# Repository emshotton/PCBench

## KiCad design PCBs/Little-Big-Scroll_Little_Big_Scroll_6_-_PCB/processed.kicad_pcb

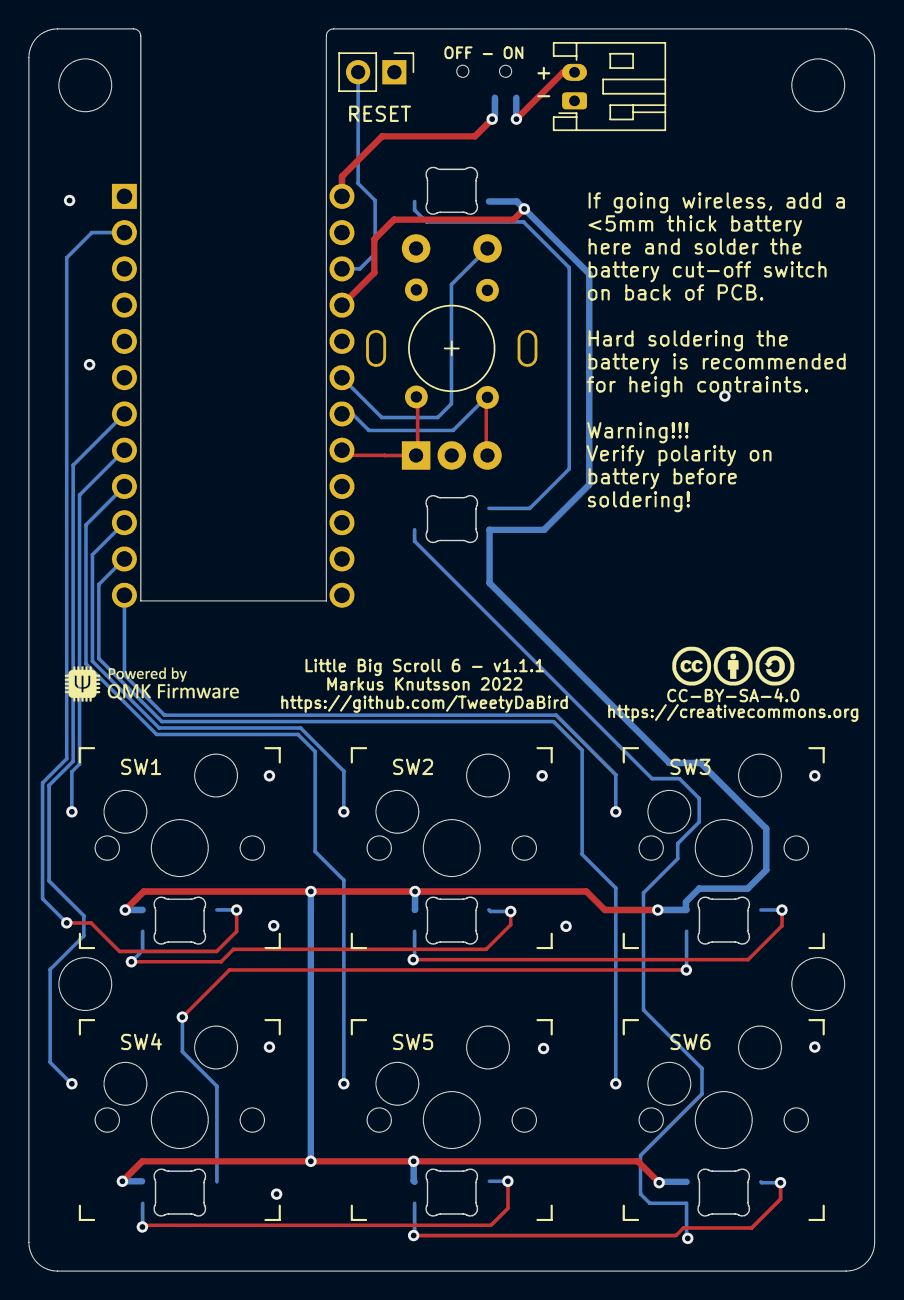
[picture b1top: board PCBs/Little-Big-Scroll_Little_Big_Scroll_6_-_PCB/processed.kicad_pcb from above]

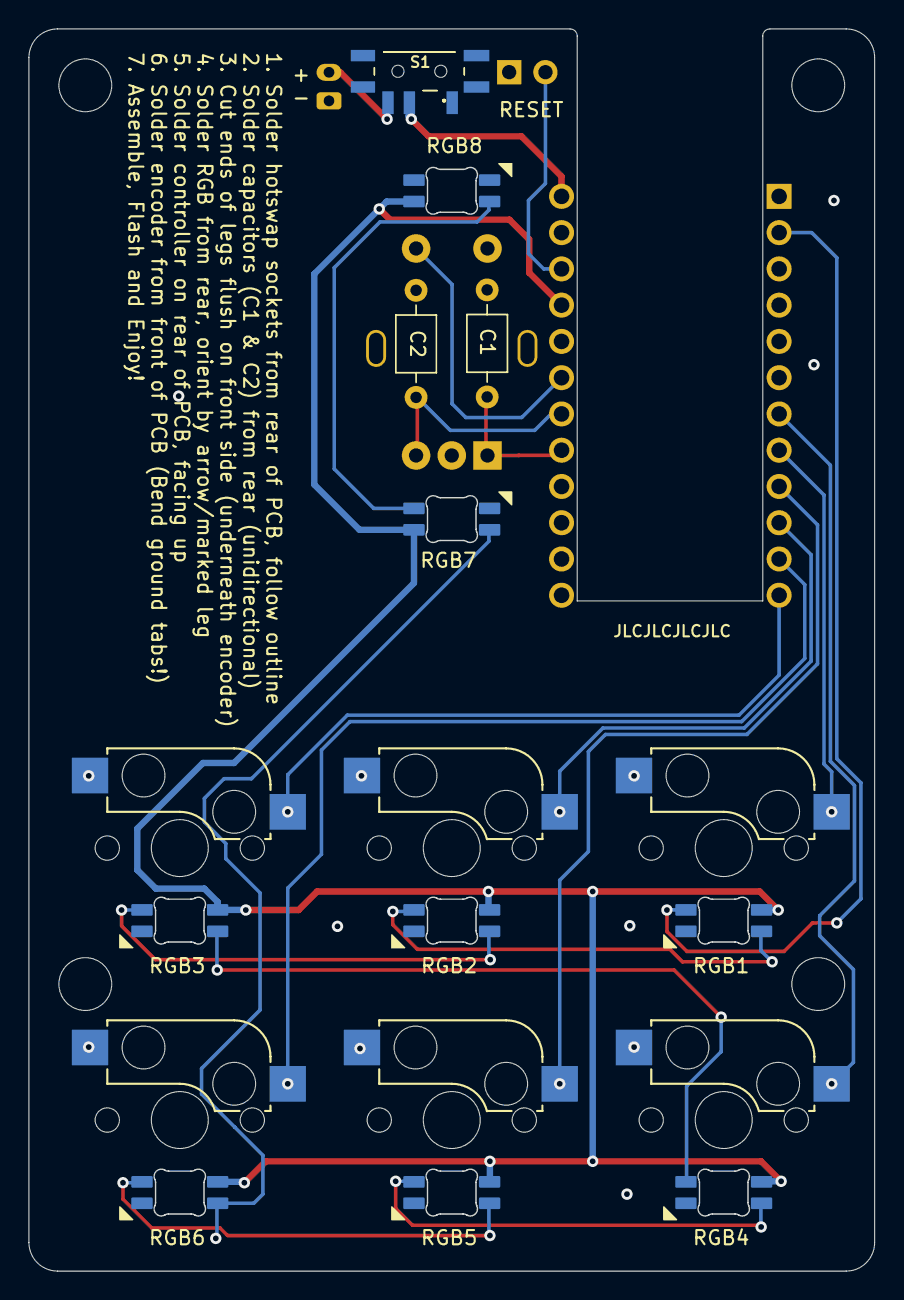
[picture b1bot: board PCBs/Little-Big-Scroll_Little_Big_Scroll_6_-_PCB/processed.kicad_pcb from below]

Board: 2 copper layers, 59.2 x 87.0 mm, 27 parts (3 on the bottom side), 22 nets.

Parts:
C1, C2: C_Small; C_Axial_L3.8mm_D2.6mm_P7.50mm_Horizontal
ENC1: Rotary_Encoder_Click; Encoder_Alps_EC11E_Small
H1, H2, H3, H4: Spacer_PCB; Spacer PCB hole
J1: Conn_01x02; PinHeader_1x02_P2.54mm_Vertical
J2: Conn_01x02; JST_PH_S2B-PH-K_1x02_P2.00mm_Horizontal
Logo1: CC-BY-SA-4.0; CC_BY_SA_40
Logo2: QMK_Logo; Powered_by_QMK
RGB1, RGB2, RGB3, RGB4, RGB5, RGB6, RGB7, RGB8: SK6812MINI-E; RGB_SK6812MINI-E
S1: MSK12C02
SW1, SW2, SW3, SW4, SW5, SW6: SW_MX_HS; SW_MX_HotSwap
U1: ProMicro

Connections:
/BAT++: J2.2, S1.C1 (NO)
BAT+: S1.B1 (COM), U1.24 (RAW)
EncA: C1.1, ENC1.A, U1.17 (A0/PF7)
EncB: C2.2, ENC1.B, U1.18 (A1/PF6)
EncKey: ENC1.S1, U1.19 (A2/PF5)
GND: C1.2, C2.1, ENC1.C, ENC1.MP1 (GND), ENC1.MP2 (GND), ENC1.S2, J1.1, J2.1, RGB1.3 (GND), RGB2.3 (GND), RGB3.3 (GND), RGB4.3 (GND), RGB5.3 (GND), RGB6.3 (GND), RGB7.3 (GND), RGB8.3 (GND), S1.MP, SW1.2, SW2.2, SW3.2, SW4.2, SW5.2, SW6.2, U1.3 (GND), U1.4 (GND), U1.23 (GND)
Key1: SW1.1, U1.8 (5/PC6)
Key2: SW2.1, U1.10 (7/PE6)
Key3: SW3.1, U1.12 (9/PB5)
Key4: SW4.1, U1.7 (4/PD4)
Key5: SW5.1, U1.9 (6/PD7)
Key6: SW6.1, U1.11 (8/PB4)
unnamed: J1.2, U1.22 (RST)
unnamed: RGB1.2 (DOUT), RGB2.4 (DIN)
unnamed: RGB2.2 (DOUT), RGB3.4 (DIN)
unnamed: RGB3.2 (DOUT), RGB4.4 (DIN)
unnamed: RGB4.2 (DOUT), RGB5.4 (DIN)
unnamed: RGB5.2 (DOUT), RGB6.4 (DIN)
unnamed: RGB6.2 (DOUT), RGB7.4 (DIN)
unnamed: RGB7.2 (DOUT), RGB8.4 (DIN)
RGB: RGB1.4 (DIN), U1.2 (RX1/PD2)
VCC: RGB1.1 (VDD), RGB2.1 (VDD), RGB3.1 (VDD), RGB4.1 (VDD), RGB5.1 (VDD), RGB6.1 (VDD), RGB7.1 (VDD), RGB8.1 (VDD), U1.21 (VCC)

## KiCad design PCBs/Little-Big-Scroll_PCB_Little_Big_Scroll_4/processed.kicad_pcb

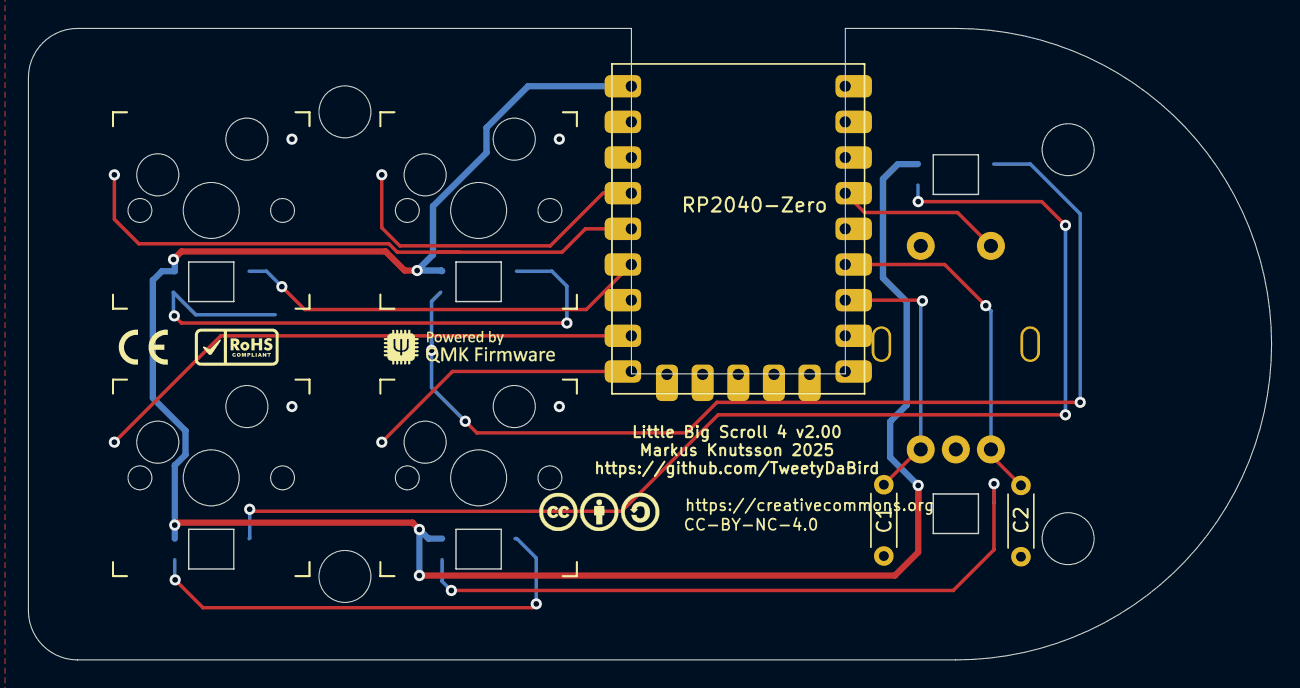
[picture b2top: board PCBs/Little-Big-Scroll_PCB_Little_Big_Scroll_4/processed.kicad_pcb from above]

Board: 2 copper layers, 88.6 x 45.0 mm, 22 parts (0 on the bottom side), 15 nets.

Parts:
C1, C2: 100nF; R_Axial_DIN0204_L3.6mm_D1.6mm_P5.08mm_Horizontal
ENC1: Rotary_Encoder_Click; Encoder_Alps_EC11E_Small
H1, H2, H3, H4: Spacer_PCB; Spacer PCB hole
Logo1: CC-BY-NC-4.0; CC_BY_SA_40_line
Logo2: QMK_Logo; Powered_by_QMK
Logo3: RoHS; RoHs
Logo4: CE
RGB1, RGB2, RGB3, RGB4, RGB5, RGB6: SK6812MINI-E; RGB_SK6812MINI-E
RZ1: RP2040-Zero; RP2040-Zero_castellated
SW1, SW2, SW3, SW4: SW_Push; SW_MX_HotSwap

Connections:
ENC_A: C1.1, ENC1.A, RZ1.7 (GP6)
ENC_B: C2.2, ENC1.B, RZ1.6 (GP5)
GND: C1.2, C2.1, ENC1.C, ENC1.MP (GND), ENC1.S2, RGB1.3 (GND), RGB2.3 (GND), RGB3.3 (GND), RGB4.3 (GND), RGB5.3 (GND), RGB6.3 (GND), RZ1.22 (GND), SW1.2, SW2.2, SW3.2, SW4.2
Key1: RZ1.19 (GP28), SW1.1
Key2: RZ1.20 (GP29), SW2.1
Key3: RZ1.16 (GP15), SW3.1
Key4: RZ1.15 (GP14), SW4.1
Key5: ENC1.S1, RZ1.4 (GP3)
unnamed: RGB1.2 (DOUT), RGB2.4 (DIN)
unnamed: RGB2.2 (DOUT), RGB3.4 (DIN)
unnamed: RGB3.2 (DOUT), RGB4.4 (DIN)
unnamed: RGB4.2 (DOUT), RGB5.4 (DIN)
unnamed: RGB5.2 (DOUT), RGB6.4 (DIN)
RGB: RGB1.4 (DIN), RZ1.18 (GP27)
VCC: RGB1.1 (VDD), RGB2.1 (VDD), RGB3.1 (VDD), RGB4.1 (VDD), RGB5.1 (VDD), RGB6.1 (VDD), RZ1.23 (5V)

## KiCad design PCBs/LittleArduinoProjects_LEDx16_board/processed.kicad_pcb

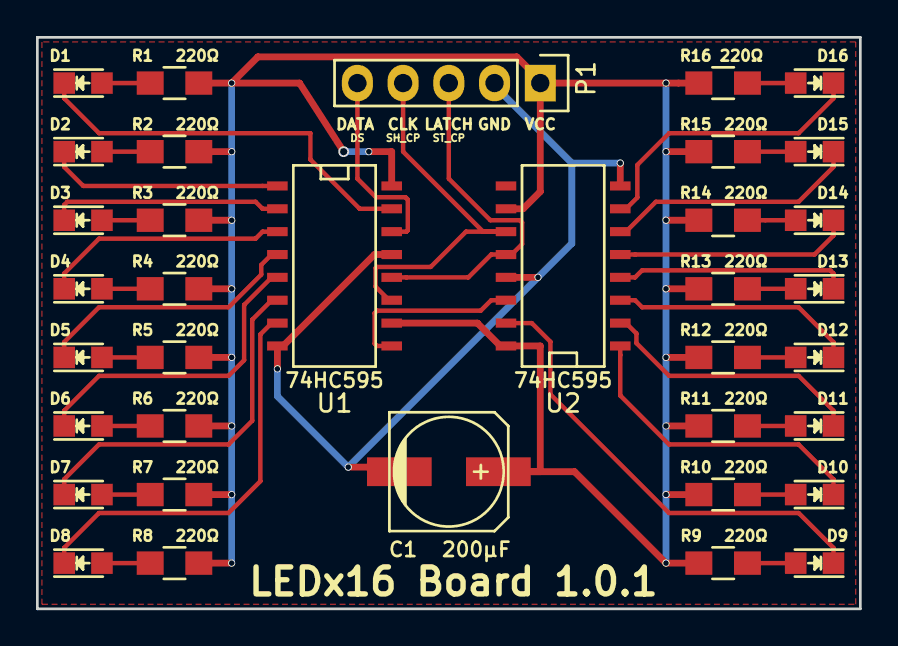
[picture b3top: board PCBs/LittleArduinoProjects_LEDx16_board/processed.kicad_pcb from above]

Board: 2 copper layers, 45.7 x 31.8 mm, 36 parts (0 on the bottom side), 38 nets.

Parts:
C1: 200µF; c_elec_6.3x5.3
D1, D2, D3, D4, D5, D6, D7, D8, D9, D10, D11, D12, D13, D14, D15, D16: LED; LED_0805
P1: CONN_01X05; Pin_Header_Straight_1x05
R1, R2, R3, R4, R5, R6, R7, R8, R9, R10, R11, R12, R13, R14, R15, R16: 220Ω; R_0805_HandSoldering
U1, U2: 74HC595; SO-16-N

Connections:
/CARRY: U1.9, U2.14
/CLOCK: P1.4, U1.11, U2.11
/DATA: P1.5, U1.14
/LATCH: P1.3, U1.12, U2.12
/led_1_1: D1.1, U1.15
/led_1_2: D2.1, U1.1
/led_1_3: D3.1, U1.2
/led_1_4: D4.1, U1.3
/led_1_5: D5.1, U1.4
/led_1_6: D6.1, U1.5
/led_1_7: D7.1, U1.6
/led_1_8: D8.1, U1.7
/led_2_1: D9.1, U2.15
/led_2_2: D10.1, U2.1
/led_2_3: D11.1, U2.2
/led_2_4: D12.1, U2.3
/led_2_5: D13.1, U2.4
/led_2_6: D14.1, U2.5
/led_2_7: D15.1, U2.6
/led_2_8: D16.1, U2.7
GND: C1.2, P1.2, U1.8, U1.13, U2.8, U2.13
unnamed: D1.2, R1.1
unnamed: D2.2, R2.1
unnamed: D3.2, R3.1
unnamed: D4.2, R4.1
unnamed: D5.2, R5.1
unnamed: D6.2, R6.1
unnamed: D7.2, R7.1
unnamed: D8.2, R8.1
unnamed: D9.2, R9.1
unnamed: D10.2, R10.1
unnamed: D11.2, R11.1
unnamed: D12.2, R12.1
unnamed: D13.2, R13.1
unnamed: D14.2, R14.1
unnamed: D15.2, R15.1
unnamed: D16.2, R16.1
VCC: C1.1, P1.1, R1.2, R2.2, R3.2, R4.2, R5.2, R6.2, R7.2, R8.2, R9.2, R10.2, R11.2, R12.2, R13.2, R14.2, R15.2, R16.2, U1.10, U1.16, U2.10, U2.16

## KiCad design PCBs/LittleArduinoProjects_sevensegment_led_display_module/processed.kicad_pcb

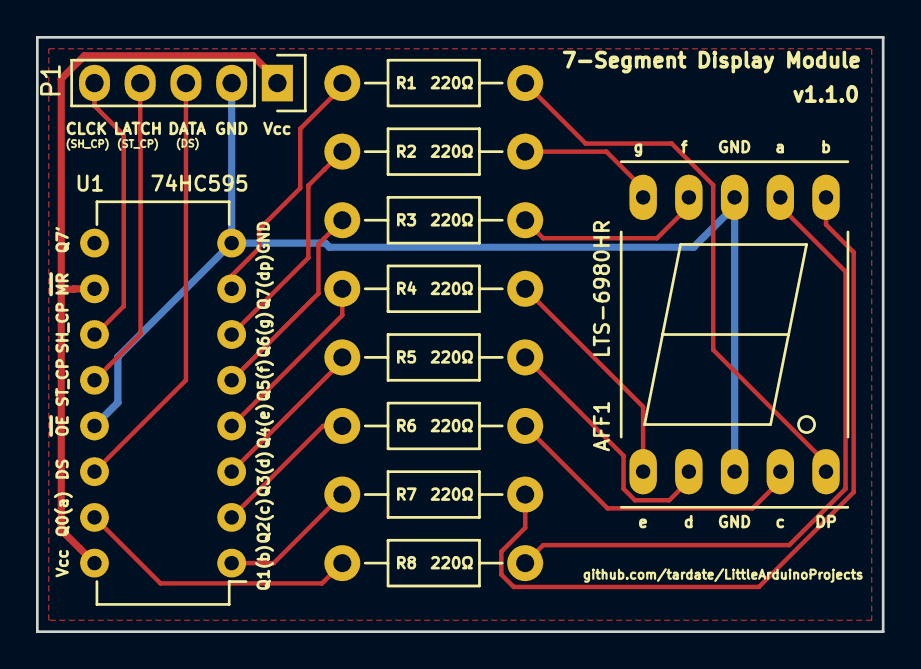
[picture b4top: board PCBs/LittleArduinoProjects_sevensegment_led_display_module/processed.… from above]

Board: 2 copper layers, 47.0 x 33.0 mm, 11 parts (0 on the bottom side), 21 nets.

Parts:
AFF1: LTS-6980HR; 7SegmentLED_LTS6760_LTS6780
P1: CONN_01X05; Pin_Header_Straight_1x05
R1, R2, R3, R4, R5, R6, R7, R8: 220Ω; Resistor_Horizontal_RM10mm
U1: 74HC595; DIP-16_W7.62mm

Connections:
/CLK: P1.5, U1.11
/DATA: P1.3, U1.14
/LATCH: P1.4, U1.12
/ssA: R8.1, U1.15
/ssB: R7.1, U1.1
/ssC: R6.1, U1.2
/ssD: R5.1, U1.3
/ssDP: R1.1, U1.7
/ssE: R4.1, U1.4
/ssF: R3.1, U1.5
/ssG: R2.1, U1.6
GND: AFF1.3, AFF1.8, P1.2, U1.8, U1.13
unnamed: AFF1.1, R4.2
unnamed: AFF1.2, R5.2
unnamed: AFF1.4, R6.2
unnamed: AFF1.5, R1.2
unnamed: AFF1.6, R7.2
unnamed: AFF1.7, R8.2
unnamed: AFF1.9, R3.2
unnamed: AFF1.10, R2.2
VCC: P1.1, U1.10, U1.16

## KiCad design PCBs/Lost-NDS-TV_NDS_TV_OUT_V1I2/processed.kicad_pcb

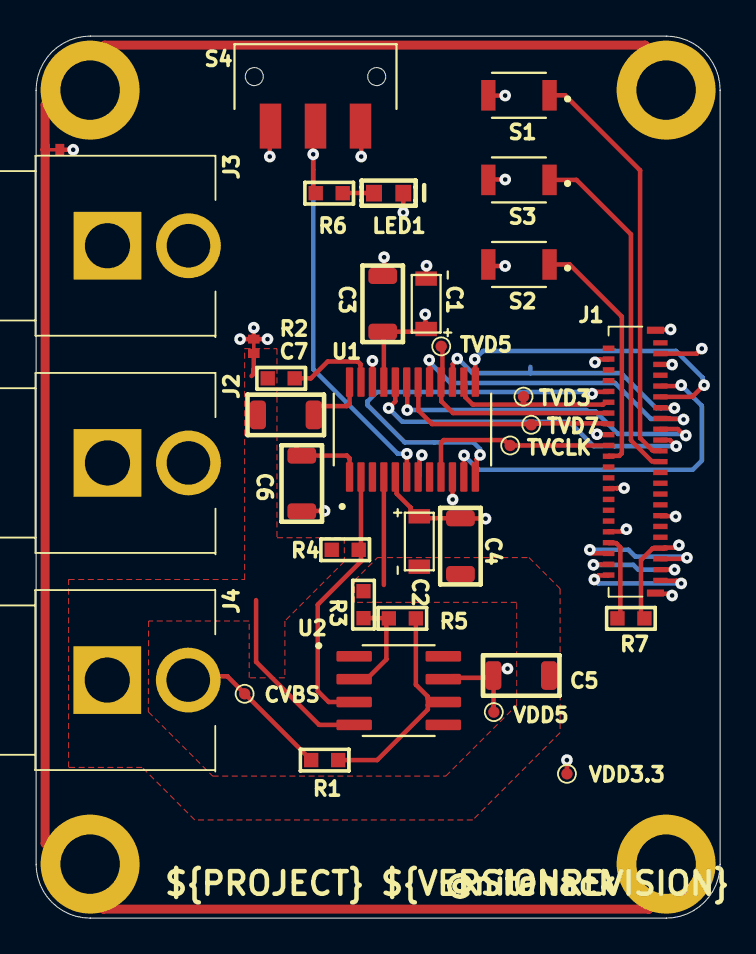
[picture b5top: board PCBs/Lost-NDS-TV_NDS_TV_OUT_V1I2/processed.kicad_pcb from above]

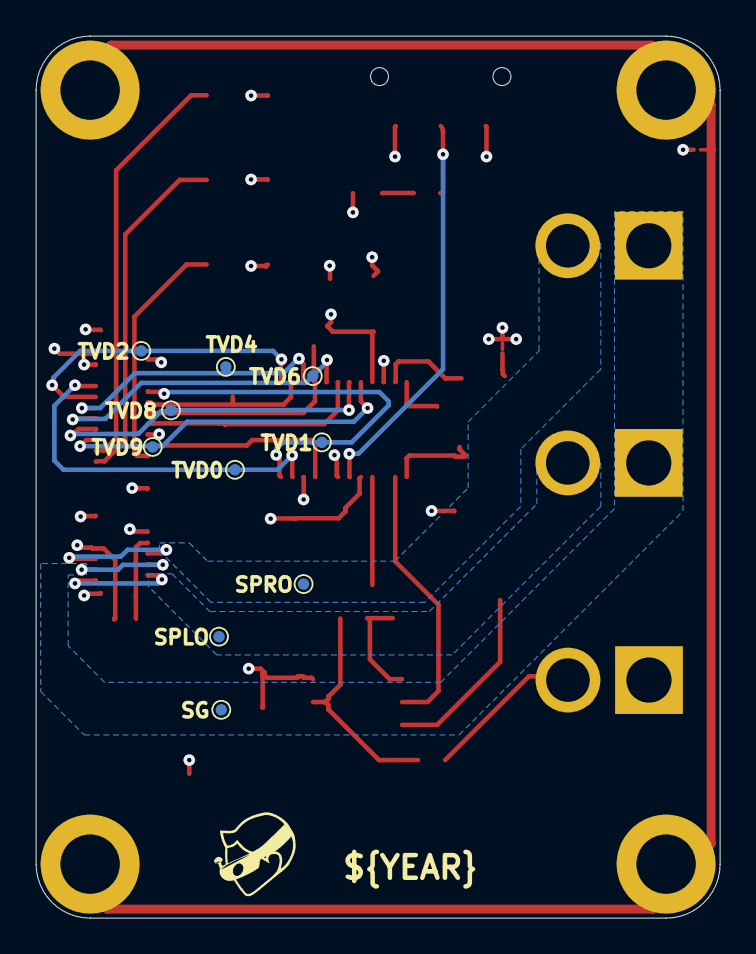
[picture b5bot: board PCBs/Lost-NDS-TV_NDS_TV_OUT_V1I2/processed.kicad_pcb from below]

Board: 4 copper layers, 38.0 x 49.0 mm, 44 parts (10 on the bottom side), 32 nets.

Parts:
C1, C2: 10uF; C1206T
C3, C4, C5, C6, C7: 0.1uF; C1206
CVBS: TP_25MILC; TP_25C
J1: 4-2328724-5; 423287245
J2: KLPX-0848A-2-W; KLPX0848A2W
J3: KLPX-0848A-2-R; KLPX0848A2R
J4: KLPX-0848A-2-Y; KLPX0848A2Y
LED1: APTD1608LZGCK; RESC0603X55N
R1: 75R; R0603
R2, R4: DNP; R0603
R3: 430R; R0603
R5, R7: 1K; R0603
R6: 320R; R0603
S1, S2, S3: B3U-1000P; SW_B3U-1000P
S4: JS102011SAQN; SW_JS102011SAQN
SG: TP_25MILC; TP_25C
SPLO: TP_25MILC; TP_25C
SPRO: TP_25MILC; TP_25C
T1, T2: NET TIE; NET_TIE
TVCLK: TP_25MILC; TP_25C
TVD0, TVD1, TVD2, TVD3, TVD4, TVD5, TVD6, TVD7, TVD8, TVD9: TP_25MILC; TP_25C
U1: MAX5184BEEG+; SOP63P602X175-24N
U2: MAX4414ESA+; SOIC127P600X175-8N
VDD3.3, VDD5: TP_25MILC; TP_25C

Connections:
+3.3V: C1.1, C2.1, C3.2, C4.2, C6.1, J1.41, S4.1, U1.5, U1.21, VDD3.3.1
+5V: C5.2, J1.43, U2.7, VDD5.1
AGND: C2.2, C4.1, C5.1, C7.1, J4.1, R2.1, R3.1, R4.1, T1.1, U1.4, U2.4
GND: C1.2, C3.1, J1.10, J1.13, J1.18, J1.28, J1.42, J1.46, J1.47, LED1.1, S1.2, S2.2, S3.2, S4.3, T1.2, T2.2, U1.7, U1.10, U1.22
LEDA2: J1.8, R7.1
LEDC2: J1.7, R7.2
NetC6_2: C6.2, U1.1
NetC7_2: C7.2, U1.24
NetCVBS_1: CVBS.1, J4.2, R1.2
NetLED1_2: LED1.2, R6.1
NetR1_1: R1.1, R5.2, U2.6
NetR2_2: R2.2, U1.23
NetR3_2: R3.2, R5.1, U2.2
NetR4_2: R4.2, U1.2, U2.3
NetR6_2: R6.2, S4.2, U1.6
P10: J1.25, S1.1
P11: J1.24, S2.1
P12: J1.23, S3.1
SG: J1.3, J1.4, J2.1, J3.1, SG.1
SPLO: J1.1, J1.2, J2.2, SPLO.1
SPRO: J1.5, J1.6, J3.2, SPRO.1
TVCLK: J1.26, TVCLK.1, U1.9
TVDATA0: J1.37, TVD0.1, U1.11
TVDATA1: J1.36, TVD1.1, U1.12
TVDATA2: J1.35, TVD2.1, U1.13
TVDATA3: J1.34, TVD3.1, U1.14
TVDATA4: J1.33, TVD4.1, U1.15
TVDATA5: J1.32, TVD5.1, U1.16
TVDATA6: J1.31, TVD6.1, U1.17
TVDATA7: J1.30, TVD7.1, U1.18
TVDATA8: J1.29, TVD8.1, U1.19
TVDATA9: J1.27, TVD9.1, U1.20

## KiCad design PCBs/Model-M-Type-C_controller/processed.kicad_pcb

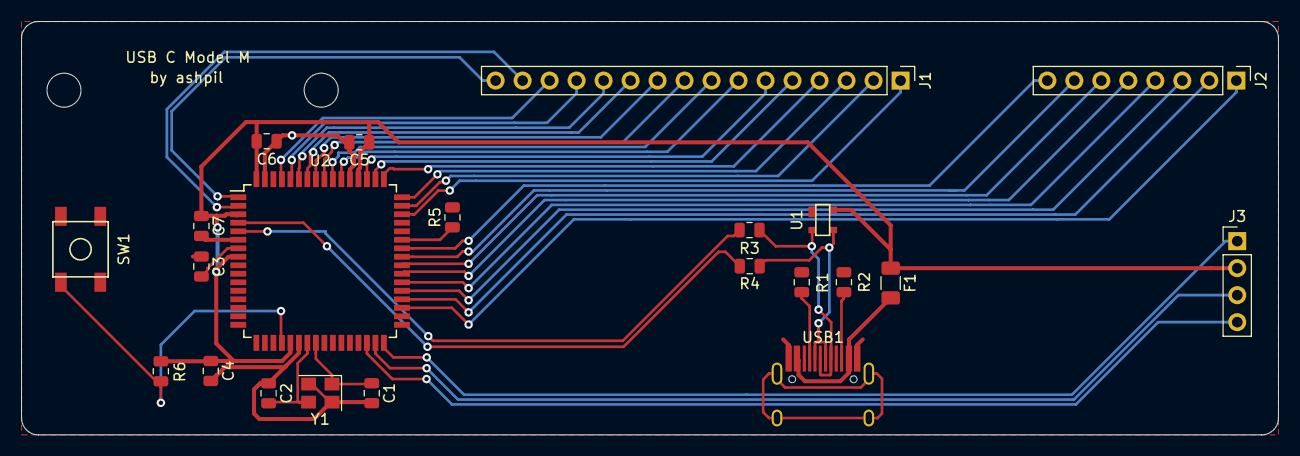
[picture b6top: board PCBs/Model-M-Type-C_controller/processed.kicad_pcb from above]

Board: 2 copper layers, 118.3 x 38.9 mm, 22 parts (0 on the bottom side), 41 nets.

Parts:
C1, C2: 22pF; C_0805_2012Metric
C3: 1uF; C_0805_2012Metric
C4, C5, C6: 0.1uF; C_0805_2012Metric
C7: 10uF; C_0805_2012Metric
F1: 500mA; Fuse_1206_3216Metric
J1: Conn_01x16; PinHeader_1x16_P2.54mm_Vertical
J2: Conn_01x08; PinHeader_1x08_P2.54mm_Vertical
J3: Conn_01x04; PinHeader_1x04_P2.54mm_Vertical
R1, R2: 5.1k; R_0805_2012Metric
R3, R4: 22; R_0805_2012Metric
R5, R6: 10k; R_0805_2012Metric
SW1: SW_Push; SKQG-1155865
U1: PRTR5V0U2X; SOT143B
U2: AT90USB1286-AU; TQFP-64_14x14mm_P0.8mm
USB1: HRO-TYPE-C-31-M-12; HRO-TYPE-C-31-M-12-HandSoldering
Y1: 16MHz; Crystal_SMD_3225-4Pin_3.2x2.5mm

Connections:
1: J1.1, U2.46
2: J1.2, U2.47
3: J1.3, U2.48
4: J1.4, U2.49
5: J1.5, U2.50
6: J1.6, U2.51
+5V: C4.1, C5.1, C6.1, C7.1, F1.1, J3.2, R6.1, U1.4, U2.3, U2.8, U2.21, U2.52, U2.64
D+: R3.2, U1.2, USB1.6, USB1.8
D-: R4.1, U1.3, USB1.5, USB1.7
GND: C1.2, C2.1, C3.2, C4.2, C5.2, C6.2, C7.2, R1.2, R2.2, R5.2, SW1.1, U1.1, U2.6, U2.22, U2.53, U2.63, USB1.1, USB1.12, Y1.2, Y1.4
unnamed: C1.1, U2.24, Y1.1
unnamed: C2.2, U2.23, Y1.3
unnamed: C3.1, U2.7
unnamed: J1.7, U2.54
unnamed: J1.8, U2.55
unnamed: J1.9, U2.56
unnamed: J1.10, U2.57
unnamed: J1.11, U2.58
unnamed: J1.12, U2.59
unnamed: J1.13, U2.60
unnamed: J1.14, U2.61
unnamed: J1.15, U2.2
unnamed: J1.16, U2.1
unnamed: J2.1, U2.35
unnamed: J2.2, U2.36
unnamed: J2.3, U2.37
unnamed: J2.4, U2.38
unnamed: J2.5, U2.39
unnamed: J2.6, U2.40
unnamed: J2.7, U2.41
unnamed: J2.8, U2.42
unnamed: J3.1, U2.32
unnamed: J3.3, U2.31
unnamed: J3.4, U2.30
unnamed: R1.1, USB1.4
unnamed: R2.1, USB1.10
unnamed: R3.1, U2.5
unnamed: R4.2, U2.4
unnamed: R5.1, U2.43
unnamed: R6.2, SW1.2, U2.20
VCC: F1.2, USB1.2, USB1.11

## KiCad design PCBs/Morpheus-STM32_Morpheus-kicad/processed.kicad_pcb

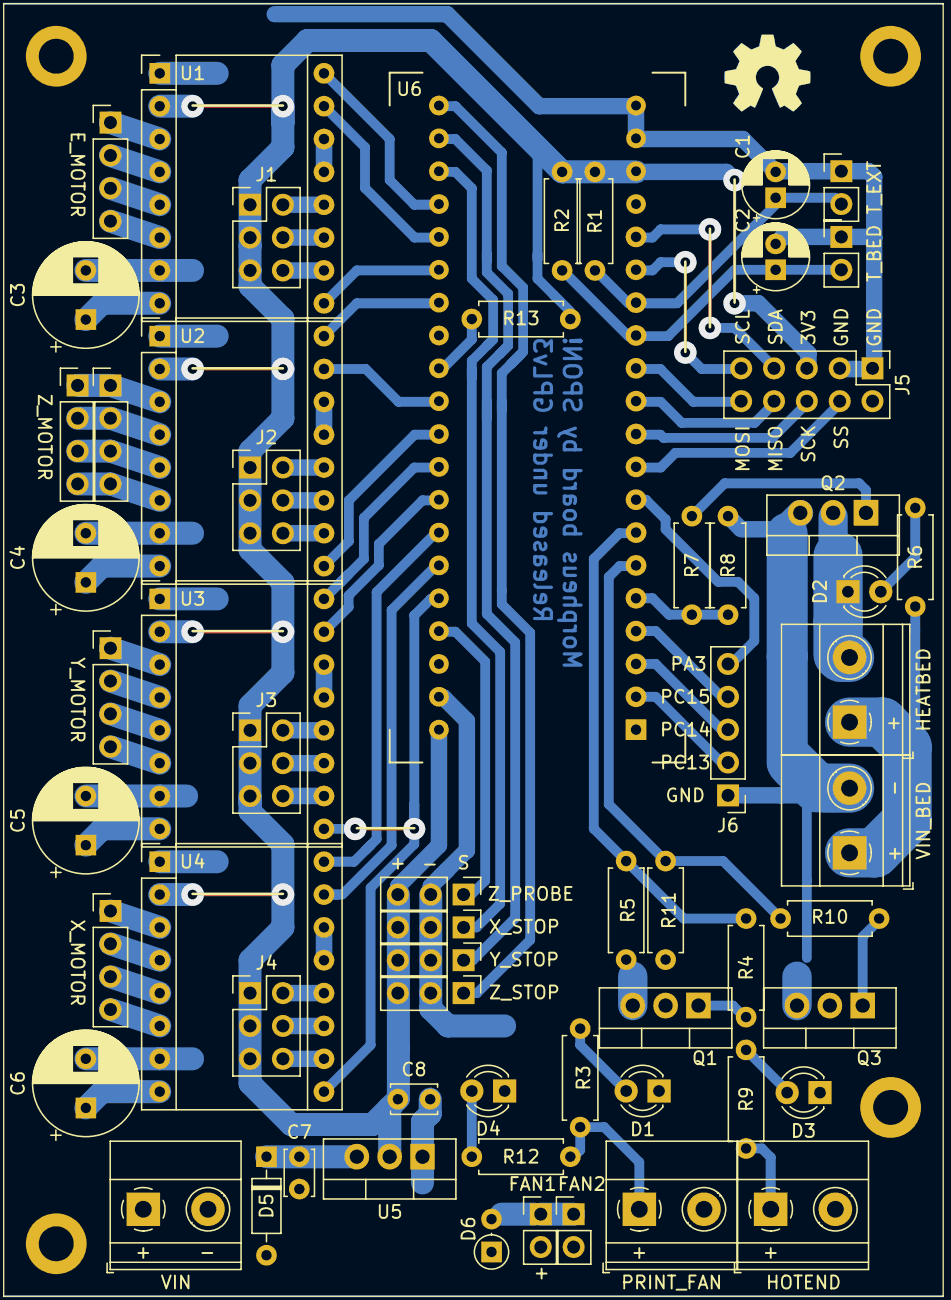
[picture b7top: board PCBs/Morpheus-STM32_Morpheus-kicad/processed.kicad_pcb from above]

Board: 2 copper layers, 60 parts (0 on the bottom side), 78 nets.

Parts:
C1, C2: 10uF10v; CP_Radial_D5.0mm_P2.00mm
C3, C4, C5, C6: 470uF16v; CP_Radial_D8.0mm_P3.80mm
C7, C8: 0.1uF; C_Disc_D3.4mm_W2.1mm_P2.50mm
D1, D2, D3: LED_Small; LED_D3.0mm
D4: LED_Small; LED_D3.0mm_Clear
D5: 1N4007; D_DO-35_SOD27_P7.62mm_Horizontal
D6: 1N4007; D_DO-35_SOD27_P2.54mm_Vertical_AnodeUp
E_MOTOR1: E_MOTOR; PinHeader_1x04_P2.54mm_Vertical
FAN1, FAN2: Conn_01x02; PinHeader_1x02_P2.54mm_Vertical
HEATBED1: HEATBED; TerminalBlock_Phoenix_MKDS-1,5-2_1x02_P5.00mm_Horizontal
HOTEND1: HOTEND; TerminalBlock_Phoenix_MKDS-1,5-2_1x02_P5.00mm_Horizontal
J1, J2, J3, J4: Conn_02x03_Odd_Even; PinHeader_2x03_P2.54mm_Vertical
J5: Conn_02x05_Counter_Clockwise; PinHeader_2x05_P2.54mm_Vertical
J6: Conn_01x05; PinHeader_1x05_P2.54mm_Vertical
PRINT_FAN1: PRINT_FAN; TerminalBlock_Phoenix_MKDS-1,5-2_1x02_P5.00mm_Horizontal
Q1, Q3: IRLZ44N; TO-220-3_Vertical
Q2: IRLB3034PBF; TO-220-3_Vertical
R1, R3, R6, R9: 1K; R_Axial_DIN0207_L6.3mm_D2.5mm_P7.62mm_Horizontal
R2, R12: 4K7; R_Axial_DIN0207_L6.3mm_D2.5mm_P7.62mm_Horizontal
R4, R7, R10: 10R; R_Axial_DIN0207_L6.3mm_D2.5mm_P7.62mm_Horizontal
R5, R8, R11: 100K; R_Axial_DIN0207_L6.3mm_D2.5mm_P7.62mm_Horizontal
R13: 1K8; R_Axial_DIN0207_L6.3mm_D2.5mm_P7.62mm_Horizontal
T_BED1: T_BED; PinHeader_1x02_P2.54mm_Vertical
T_EXT1: T_EXT; PinHeader_1x02_P2.54mm_Vertical
U1, U2, U3, U4: Pololu Driver; Pololu_Breakout-16_15.2x20.3mm
U5: LM1117-3.3; TO-220-3_Vertical
U6: BluePill_STM32F103C; BluePill
VIN1: VIN; TerminalBlock_Phoenix_MKDS-1,5-2_1x02_P5.00mm_Horizontal
VIN_BED1: VIN_BED; TerminalBlock_Phoenix_MKDS-1,5-2_1x02_P5.00mm_Horizontal
X_MOTOR1: X_MOTOR; PinHeader_1x04_P2.54mm_Vertical
X_STOP1: X_STOP; PinHeader_1x03_P2.54mm_Vertical
Y_MOTOR1: Y_MOTOR; PinHeader_1x04_P2.54mm_Vertical
Y_STOP1: Y_STOP; PinHeader_1x03_P2.54mm_Vertical
Z_MOTOR1: Z_MOTOR; PinHeader_1x04_P2.54mm_Vertical
Z_MOTOR2: Conn_01x04; PinHeader_1x04_P2.54mm_Vertical
Z_PROBE1: Z_PROBE; PinHeader_1x03_P2.54mm_Vertical
Z_STOP1: Z_STOP; PinHeader_1x03_P2.54mm_Vertical

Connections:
+3V3: C8.1, J1.1, J1.3, J1.5, J2.1, J2.3, J2.5, J3.1, J3.3, J3.5, J4.1, J4.3, J4.5, J5.5, R1.1, R2.1, R13.1, U1.2, U2.2, U3.2, U4.2, U5.2, U6.18, U6.40, X_STOP1.3, Y_STOP1.3, Z_PROBE1.3, Z_STOP1.3
+12P: HEATBED1.1, R6.2, VIN_BED1.1
+12V: C3.1, C4.1, C5.1, C6.1, D5.2, D6.1, FAN1.2, FAN2.2, HOTEND1.1, PRINT_FAN1.1, R3.2, R9.2, R12.2, U1.8, U2.8, U3.8, U4.8, VIN1.1
E_DIR: U1.16, U6.24
E_ENABLE: U1.9, U6.26
E_STEP: U1.15, U6.25
GND: C1.2, C2.2, C3.2, C4.2, C5.2, C6.2, C7.2, C8.2, D4.1, D6.2, FAN1.1, FAN2.1, J5.1, J5.3, J6.1, Q1.3, Q2.3, Q3.3, R5.1, R8.1, R11.1, T_BED1.1, T_EXT1.1, U1.1, U1.7, U2.1, U2.7, U3.1, U3.7, U4.1, U4.7, U5.1, U6.19, U6.20, U6.39, VIN1.2, VIN_BED1.2, X_STOP1.2, Y_STOP1.2, Z_PROBE1.2, Z_STOP1.2
HEATER_BED: R7.2, R8.2, U6.5
HOTEND: R10.2, R11.2, U6.6
MISO: J5.8, U6.11
MOSI: J5.10, U6.12
unnamed: C7.1, D5.1, U5.3
unnamed: D1.1, PRINT_FAN1.2, Q1.2
unnamed: D1.2, R3.1
unnamed: D2.1, HEATBED1.2, Q2.2
unnamed: D2.2, R6.1
unnamed: D3.1, HOTEND1.2, Q3.2
unnamed: D3.2, R9.1
unnamed: D4.2, R12.1
unnamed: E_MOTOR1.1, U1.3
unnamed: E_MOTOR1.2, U1.4
unnamed: E_MOTOR1.3, U1.5
unnamed: E_MOTOR1.4, U1.6
unnamed: J1.2, U1.12
unnamed: J1.4, U1.11
unnamed: J1.6, U1.10
unnamed: J2.2, U2.12
unnamed: J2.4, U2.11
unnamed: J2.6, U2.10
unnamed: J3.2, U3.12
unnamed: J3.4, U3.11
unnamed: J3.6, U3.10
unnamed: J4.2, U4.12
unnamed: J4.4, U4.11
unnamed: J4.6, U4.10
unnamed: Q1.1, R4.1
unnamed: Q2.1, R7.1
unnamed: Q3.1, R10.1
unnamed: U1.13, U1.14
unnamed: U2.3, Z_MOTOR1.1, Z_MOTOR2.1
unnamed: U2.4, Z_MOTOR1.2, Z_MOTOR2.2
unnamed: U2.5, Z_MOTOR1.3, Z_MOTOR2.3
unnamed: U2.6, Z_MOTOR1.4, Z_MOTOR2.4
unnamed: U2.13, U2.14
unnamed: U3.3, Y_MOTOR1.1
unnamed: U3.4, Y_MOTOR1.2
unnamed: U3.5, Y_MOTOR1.3
unnamed: U3.6, Y_MOTOR1.4
unnamed: U3.13, U3.14
unnamed: U4.3, X_MOTOR1.1
unnamed: U4.4, X_MOTOR1.2
unnamed: U4.5, X_MOTOR1.3
unnamed: U4.6, X_MOTOR1.4
unnamed: U4.13, U4.14
PA3: J6.5, U6.8
PC13: J6.2, U6.2
PC14: J6.3, U6.3
PC15: J6.4, U6.4
PRINT_FAN: R4.2, R5.2, U6.7
SCK: J5.6, U6.10
SCL: J5.9, U6.15
SDA: J5.7, U6.16
SS: J5.4, U6.9
T_BED: C2.1, R2.2, T_BED1.2, U6.13
T_HOTEND: C1.1, R1.2, T_EXT1.2, U6.14
USB_PULLUP: R13.2, U6.29
XY_ENABLE: U3.9, U4.9, U6.36
X_DIR: U4.16, U6.34
X_STEP: U4.15, U6.35
X_STOP: U6.23, X_STOP1.1
Y_DIR: U3.16, U6.32
Y_STEP: U3.15, U6.33
Y_STOP: U6.22, Y_STOP1.1
Z_DIR: U2.16, U6.27
Z_ENABLE: U2.9, U6.31
Z_PROBE: U6.37, Z_PROBE1.1
Z_STEP: U2.15, U6.30
Z_STOP: U6.21, Z_STOP1.1

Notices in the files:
PCBs/Little-Big-Scroll_Little_Big_Scroll_6_-_PCB/processed.kicad_pcb:
Licensed under Creative Commons BY-SA 4.0 International
PCBs/Little-Big-Scroll_PCB_Little_Big_Scroll_4/processed.kicad_pcb:
Licensed under Creative Commons Attribution-ShareAlike 4.0 International
PCBs/Morpheus-STM32_Morpheus-kicad/processed.kicad_pcb:
Released under GPLv3
